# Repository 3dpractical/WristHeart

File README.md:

# WristHeart
Wearable health monitoring device for measuring human's heart rate (beat per minute) based on IoT.

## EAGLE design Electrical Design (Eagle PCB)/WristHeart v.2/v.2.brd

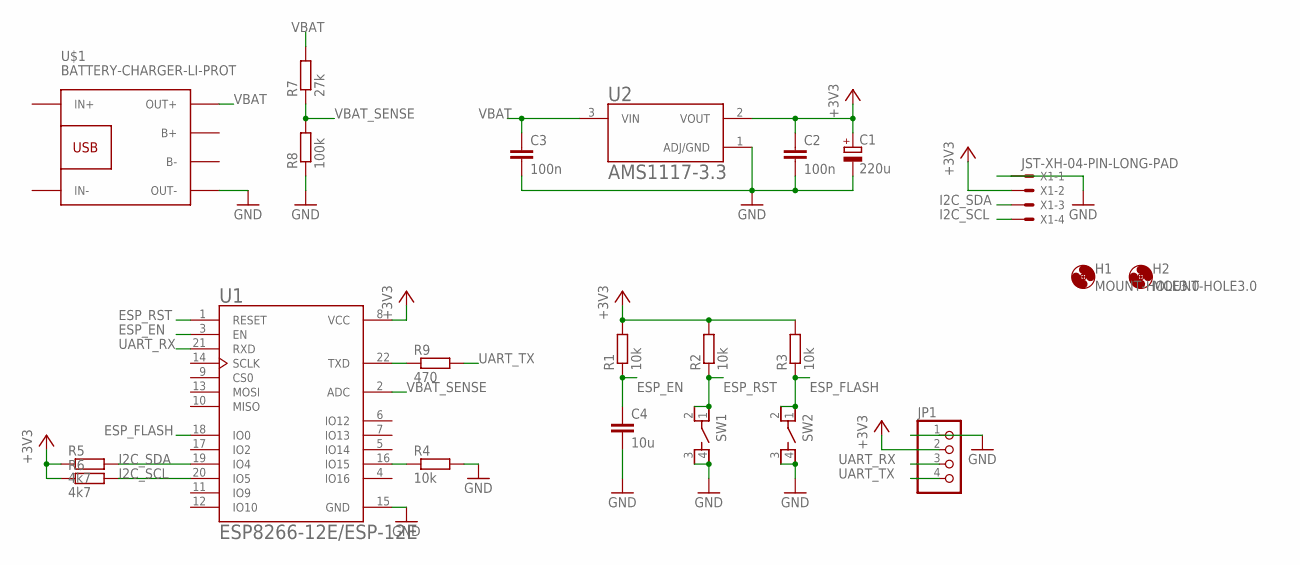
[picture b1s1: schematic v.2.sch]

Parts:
C1: 220u; 153CLV-0605
C2, C3: 100n; C0805
C4: 10u; C0805
H1, H2: MOUNT-HOLE3.0; 3,0
JP1: PINHD-1X4; 1X04
R1, R2, R3, R4: 10k; R0805
R5, R6: 4k7; R0805
R7: 27k; R0805
R8: 100k; R0805
R9: 470; R0805
SW1, SW2: PTS810_SJM_250_SMTR_LFS; SW_PTS810_SJM_250_SMTR_LFS
U1: ESP8266-12E/ESP-12E; XCVR_ESP8266-12E/ESP-12E
U2: AMS1117-3.3; SOT229P700X180-4N
U$1: BATTERY-CHARGER-LI-PROT
X1: JST-XH-04-PIN-LONG-PAD; JST-XH-04-PACKAGE-LONG-PAD

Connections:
+3V3: C1.+, C2.1, JP1.2, R1.2, R2.2, R3.2, R5.1, R6.1, U1.8 (VCC), U2.2 (VOUT), X1.2
ESP_EN: C4.1, R1.1, U1.3 (EN)
ESP_FLASH: R3.1, SW2.1, SW2.2, U1.18 (IO0)
ESP_RST: R2.1, SW1.1, SW1.2, U1.1 (RESET)
GND: C1.-, C2.2, C3.2, C4.2, JP1.1, R4.2, R8.1, SW1.3, SW1.4, SW2.3, SW2.4, U1.15 (GND), U2.1 (ADJ/GND), U$1.OUT-, X1.1
I2C_SCL: R6.2, U1.20 (IO5), X1.4
I2C_SDA: R5.2, U1.19 (IO4), X1.3
unnamed: R9.1, U1.22 (TXD)
unnamed: R4.1, U1.16 (IO15)
UART_RX: JP1.3, U1.21 (RXD)
UART_TX: JP1.4, R9.2
VBAT: C3.1, R7.2, U2.3 (VIN), U$1.OUT+
VBAT_SENSE: R7.1, R8.2, U1.2 (ADC)

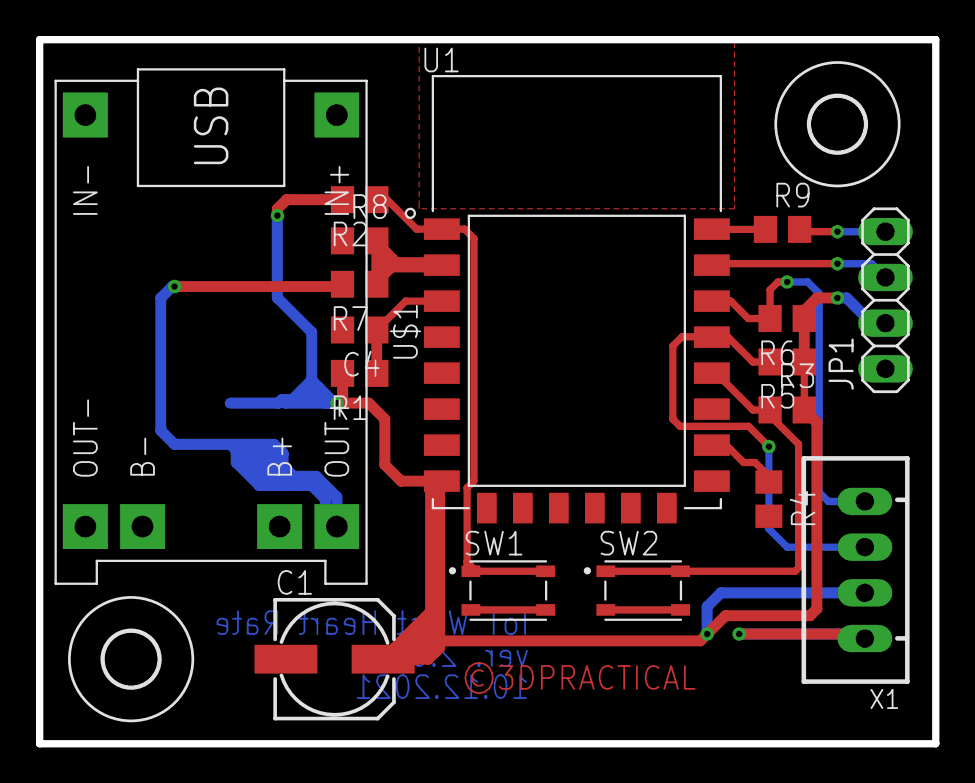
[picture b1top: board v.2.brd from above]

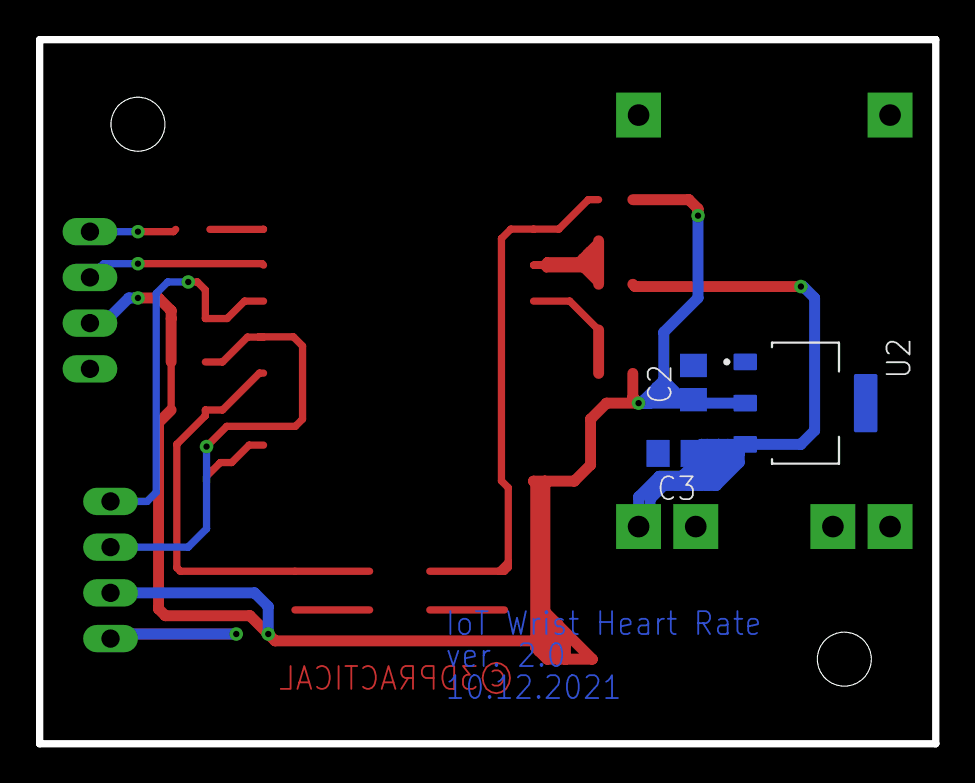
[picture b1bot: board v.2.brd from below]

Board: 2 copper layers, 49.8 x 39.1 mm, 22 parts (3 on the bottom side), 13 nets.

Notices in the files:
Electrical Design (Eagle PCB)/WristHeart v.2/v.2.brd:
©3DPRACTICAL
parts and their libraries:
diy-modules: Released under the Creative Commons Attribution 4.0 International License: http://creativecommons.org/licenses/by/4.0
